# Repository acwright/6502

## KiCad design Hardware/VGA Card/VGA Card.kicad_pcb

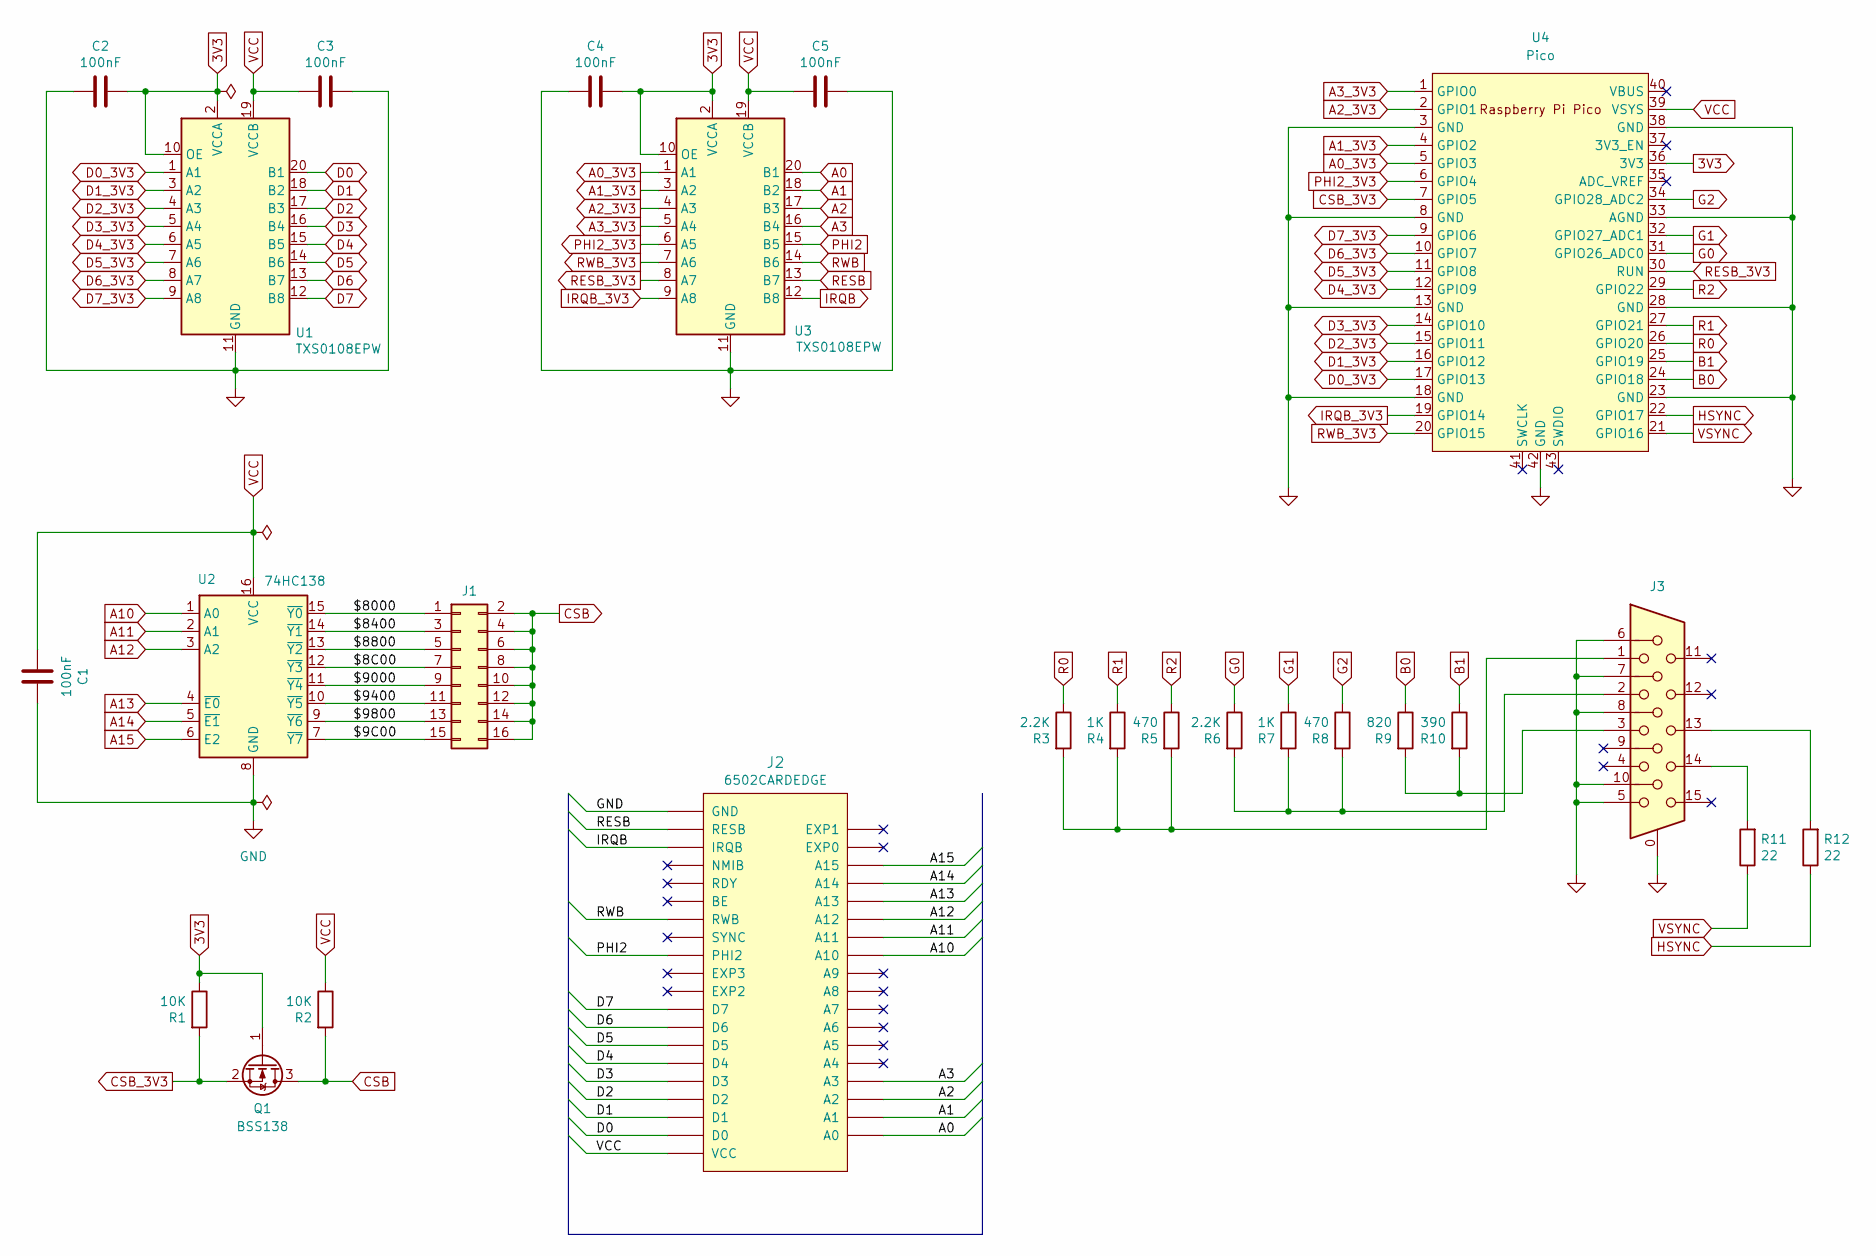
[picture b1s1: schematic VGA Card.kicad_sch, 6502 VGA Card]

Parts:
C1, C2, C3, C4, C5: 100nF; C_0805_2012Metric; LCSC C49678
J1: Conn_02x08_Odd_Even; PinHeader_2x08_P2.54mm_Vertical
J2: 6502CARDEDGE
J3: DE15_Receptacle_HighDensity_MountingHoles; DSUB-15-HD_Female_Horizontal_P2.29x1.98mm_EdgePinOffset3.03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
Q1: BSS138; SOT-23; LCSC C78284
R1, R2: 10K; R_0805_2012Metric; LCSC C17414
R3, R6: 2.2K; R_0805_2012Metric; LCSC C17520
R4, R7: 1K; R_0805_2012Metric; LCSC C17513
R5, R8: 470; R_0805_2012Metric; LCSC C17710
R9: 820; R_0805_2012Metric; LCSC C17837
R10: 390; R_0805_2012Metric; LCSC C17655
R11, R12: 22; R_0805_2012Metric; LCSC C17561
U1, U3: TXS0108EPW; TSSOP-20_4.4x6.5mm_P0.65mm; LCSC C17206
U2: 74HC138; SOIC-16_3.9x9.9mm_P1.27mm; LCSC C5602
U4: Pico; RPi_Pico_SMD_TH

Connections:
3V3: C2.1, C4.1, Q1.1 (G), R1.1, U1.2 (VCCA), U1.10 (OE), U3.2 (VCCA), U3.10 (OE), U4.36 (3V3)
/$8C00: J1.7, U2.12 (~Y3)
/$9C00: J1.15, U2.7 (~Y7)
/$8000: J1.1, U2.15 (~Y0)
/$8400: J1.3, U2.14 (~Y1)
/$8800: J1.5, U2.13 (~Y2)
/$9000: J1.9, U2.11 (~Y4)
/$9400: J1.11, U2.10 (~Y5)
/$9800: J1.13, U2.9 (~Y6)
A0: J2.A0, U3.20 (B1)
A0_3V3: U3.1 (A1), U4.5 (GPIO3)
A1: J2.A1, U3.18 (B2)
A1_3V3: U3.3 (A2), U4.4 (GPIO2)
A2: J2.A2, U3.17 (B3)
A2_3V3: U3.4 (A3), U4.2 (GPIO1)
A3: J2.A3, U3.16 (B4)
A3_3V3: U3.5 (A4), U4.1 (GPIO0)
A10: J2.A10, U2.1 (A0)
A11: J2.A11, U2.2 (A1)
A12: J2.A12, U2.3 (A2)
A13: J2.A13, U2.4 (~E0)
A14: J2.A14, U2.5 (~E1)
A15: J2.A15, U2.6 (E2)
B0: R9.1, U4.24 (GPIO18)
B1: R10.1, U4.25 (GPIO19)
CSB: J1.2, J1.4, J1.6, J1.8, J1.10, J1.12, J1.14, J1.16, Q1.3 (D), R2.2
CSB_3V3: Q1.2 (S), R1.2, U4.7 (GPIO5)
D0: J2.D0, U1.20 (B1)
D0_3V3: U1.1 (A1), U4.17 (GPIO13)
D1: J2.D1, U1.18 (B2)
D1_3V3: U1.3 (A2), U4.16 (GPIO12)
D2: J2.D2, U1.17 (B3)
D2_3V3: U1.4 (A3), U4.15 (GPIO11)
D3: J2.D3, U1.16 (B4)
D3_3V3: U1.5 (A4), U4.14 (GPIO10)
D4: J2.D4, U1.15 (B5)
D4_3V3: U1.6 (A5), U4.12 (GPIO9)
D5: J2.D5, U1.14 (B6)
D5_3V3: U1.7 (A6), U4.11 (GPIO8)
D6: J2.D6, U1.13 (B7)
D6_3V3: U1.8 (A7), U4.10 (GPIO7)
D7: J2.D7, U1.12 (B8)
D7_3V3: U1.9 (A8), U4.9 (GPIO6)
G0: R6.1, U4.31 (GPIO26_ADC0)
G1: R7.1, U4.32 (GPIO27_ADC1)
G2: R8.1, U4.34 (GPIO28_ADC2)
GND: C1.2, C2.2, C3.1, C4.2, C5.1, J2.GND, J3.0, J3.5, J3.6, J3.7, J3.8, J3.10, U1.11 (GND), U2.8 (GND), U3.11 (GND), U4.3 (GND), U4.8 (GND), U4.13 (GND), U4.18 (GND), U4.23 (GND), U4.28 (GND), U4.33 (AGND), U4.38 (GND), U4.42 (GND)
HSYNC: R12.1, U4.22 (GPIO17)
IRQB: J2.IRQB, U3.12 (B8)
IRQB_3V3: U3.9 (A8), U4.19 (GPIO14)
unnamed: J3.1, R3.2, R4.2, R5.2
unnamed: J3.2, R6.2, R7.2, R8.2
unnamed: J3.3, R9.2, R10.2
unnamed: J3.13, R12.2
unnamed: J3.14, R11.2
PHI2: J2.PHI2, U3.15 (B5)
PHI2_3V3: U3.6 (A5), U4.6 (GPIO4)
R0: R3.1, U4.26 (GPIO20)
R1: R4.1, U4.27 (GPIO21)
R2: R5.1, U4.29 (GPIO22)
RESB: J2.RESB, U3.13 (B7)
RESB_3V3: U3.8 (A7), U4.30 (RUN)
RWB: J2.RWB, U3.14 (B6)
RWB_3V3: U3.7 (A6), U4.20 (GPIO15)
VCC: C1.1, C3.2, C5.2, J2.VCC, R2.1, U1.19 (VCCB), U2.16 (VCC), U3.19 (VCCB), U4.39 (VSYS)
VSYNC: R11.1, U4.21 (GPIO16)

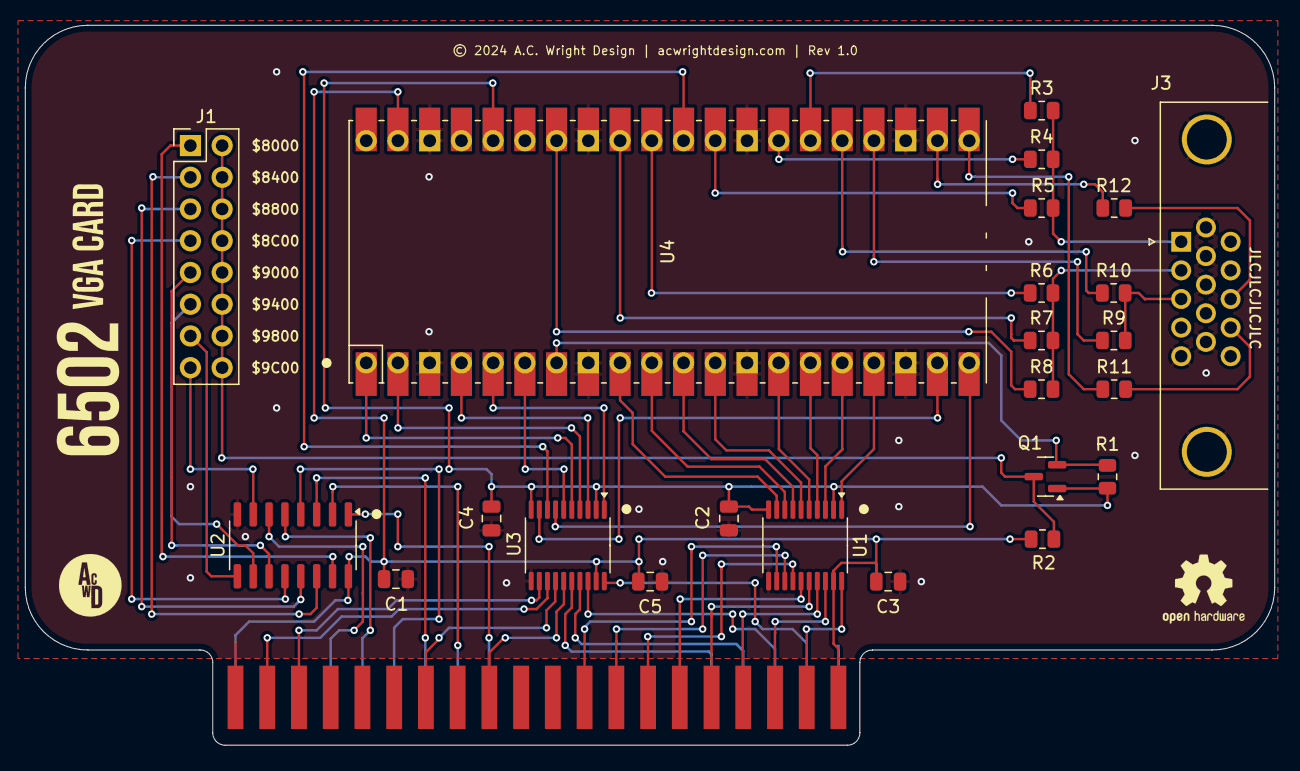
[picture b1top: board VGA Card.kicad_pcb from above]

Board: 2 copper layers, 100.0 x 57.6 mm, 25 parts (0 on the bottom side), 66 nets.

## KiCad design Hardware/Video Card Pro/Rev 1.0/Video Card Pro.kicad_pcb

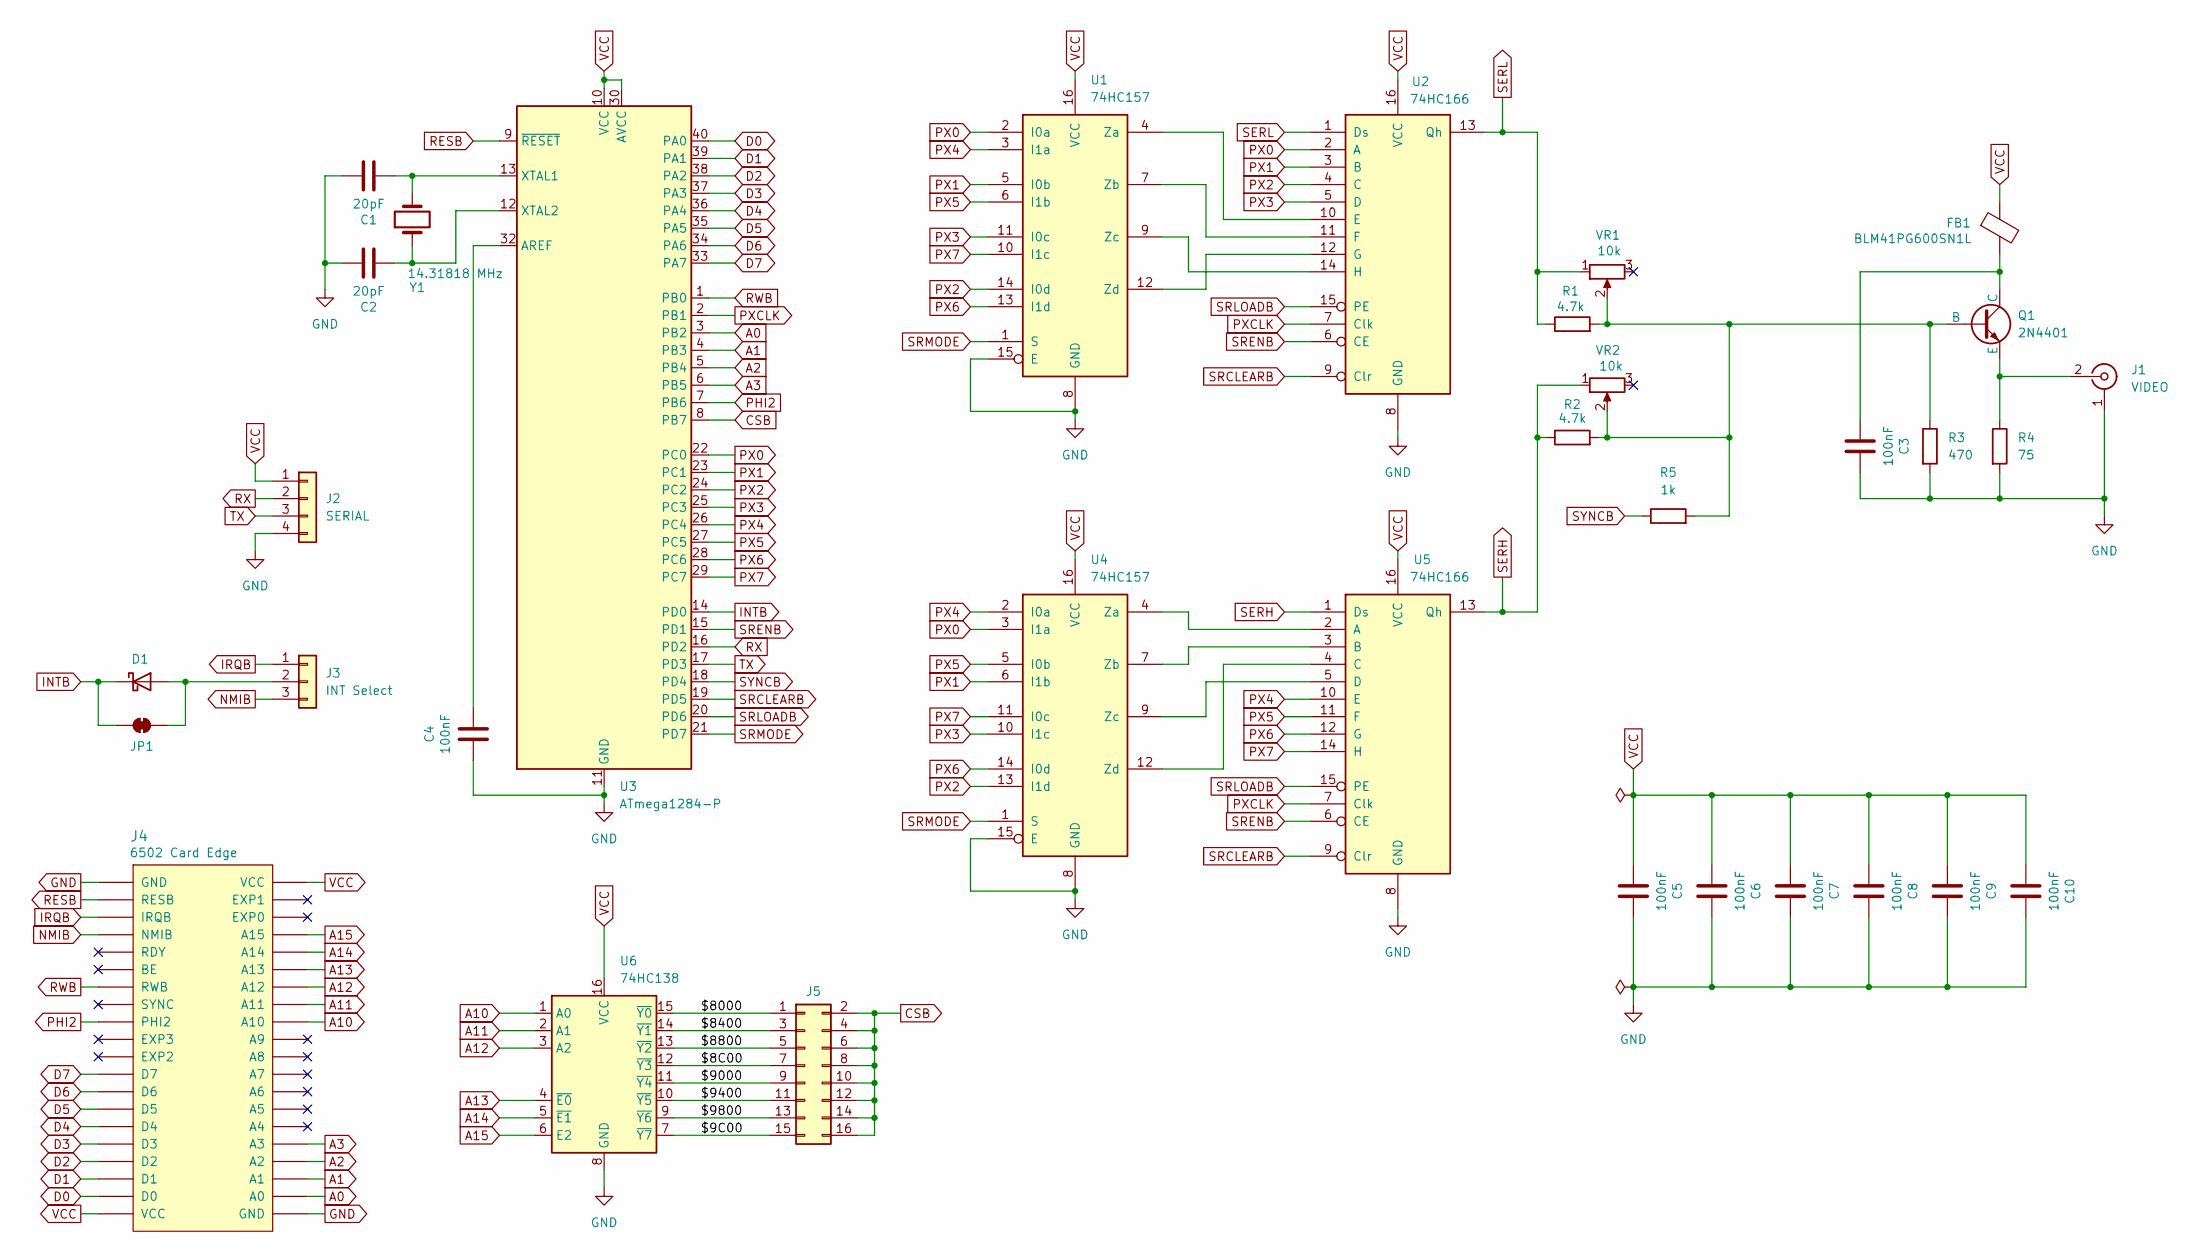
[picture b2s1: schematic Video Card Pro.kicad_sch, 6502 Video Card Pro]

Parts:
C1, C2: 20pF; C_Disc_D5.0mm_W2.5mm_P2.50mm; LCSC C105173
C3, C4, C5, C6, C7, C8, C9, C10: 100nF; C_0805_2012Metric; LCSC C49678
D1: D_Schottky; D_DO-35_SOD27_P7.62mm_Horizontal
FB1: BLM41PG600SN1L; L_1806_4516Metric; LCSC C85844
J1: VIDEO; SWITCHCRAFT_PJRAN1X1U04X
J2: SERIAL; PinHeader_1x04_P2.54mm_Vertical
J3: INT Select; PinHeader_1x03_P2.54mm_Vertical
J4: 6502 Card Edge
J5: Conn_02x08_Odd_Even; PinHeader_2x08_P2.54mm_Vertical
JP1: SolderJumper_2_Bridged; SolderJumper-2_P1.3mm_Bridged_RoundedPad1.0x1.5mm
Q1: 2N4401; TO-92_HandSolder
R1, R2: 4.7k; R_Axial_DIN0204_L3.6mm_D1.6mm_P5.08mm_Horizontal
R3: 470; R_0805_2012Metric; LCSC C17710
R4: 75; R_0805_2012Metric; LCSC C17820
R5: 1k; R_Axial_DIN0204_L3.6mm_D1.6mm_P5.08mm_Horizontal
U1, U4: 74HC157; SOIC-16_3.9x9.9mm_P1.27mm; LCSC C6823
U2, U5: 74HC166; SOIC-16_3.9x9.9mm_P1.27mm; LCSC C473363
U3: ATmega1284-P; DIP-40_W15.24mm_Socket_LongPads
U6: 74HC138; SOIC-16_3.9x9.9mm_P1.27mm; LCSC C5602
VR1, VR2: 10k; 3386F-1-103LF
Y1: 14.31818 MHz; Crystal_HC49-U_Vertical; Mouser 774-MP107-E

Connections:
/$8C00: J5.7, U6.12 (~Y3)
/$9C00: J5.15, U6.7 (~Y7)
/$8000: J5.1, U6.15 (~Y0)
/$8400: J5.3, U6.14 (~Y1)
/$8800: J5.5, U6.13 (~Y2)
/$9000: J5.9, U6.11 (~Y4)
/$9400: J5.11, U6.10 (~Y5)
/$9800: J5.13, U6.9 (~Y6)
A0: J4.A0, U3.3 (PB2)
A1: J4.A1, U3.4 (PB3)
A2: J4.A2, U3.5 (PB4)
A3: J4.A3, U3.6 (PB5)
A10: J4.A10, U6.1 (A0)
A11: J4.A11, U6.2 (A1)
A12: J4.A12, U6.3 (A2)
A13: J4.A13, U6.4 (~E0)
A14: J4.A14, U6.5 (~E1)
A15: J4.A15, U6.6 (E2)
CSB: J5.2, J5.4, J5.6, J5.8, J5.10, J5.12, J5.14, J5.16, U3.8 (PB7)
D0: J4.D0, U3.40 (PA0)
D1: J4.D1, U3.39 (PA1)
D2: J4.D2, U3.38 (PA2)
D3: J4.D3, U3.37 (PA3)
D4: J4.D4, U3.36 (PA4)
D5: J4.D5, U3.35 (PA5)
D6: J4.D6, U3.34 (PA6)
D7: J4.D7, U3.33 (PA7)
GND: C1.2, C2.2, C3.2, C4.1, C5.2, C6.2, C7.2, C8.2, C9.2, C10.2, J1.1 (Ext), J2.4, J4.GND, R3.2, R4.2, U1.8 (GND), U1.15 (E), U2.8 (GND), U3.11 (GND), U3.31 (GND), U4.8 (GND), U4.15 (E), U5.8 (GND), U6.8 (GND)
INTB: D1.1 (K), JP1.1 (A), U3.14 (PD0)
IRQB: J3.1, J4.IRQB
NMIB: J3.3, J4.NMIB
unnamed: D1.2 (A), J3.2, JP1.2 (B)
unnamed: J1.2 (In), Q1.3 (E), R4.1
unnamed: Q1.2 (B), R1.2, R2.2, R3.1, R5.2, VR1.2, VR2.2
unnamed: C3.1, FB1.2, Q1.1 (C)
unnamed: U1.4 (Za), U2.10 (E)
unnamed: U1.7 (Zb), U2.11 (F)
unnamed: U1.9 (Zc), U2.14 (H)
unnamed: U1.12 (Zd), U2.12 (G)
unnamed: C4.2, U3.32 (AREF)
unnamed: C1.1, U3.13 (XTAL1), Y1.2
unnamed: C2.1, U3.12 (XTAL2), Y1.1
unnamed: U4.4 (Za), U5.2 (A)
unnamed: U4.7 (Zb), U5.3 (B)
unnamed: U4.9 (Zc), U5.5 (D)
unnamed: U4.12 (Zd), U5.4 (C)
PHI2: J4.PHI2, U3.7 (PB6)
PX0: U1.2 (I0a), U2.2 (A), U3.22 (PC0), U4.3 (I1a)
PX1: U1.5 (I0b), U2.3 (B), U3.23 (PC1), U4.6 (I1b)
PX2: U1.14 (I0d), U2.4 (C), U3.24 (PC2), U4.13 (I1d)
PX3: U1.11 (I0c), U2.5 (D), U3.25 (PC3), U4.10 (I1c)
PX4: U1.3 (I1a), U3.26 (PC4), U4.2 (I0a), U5.10 (E)
PX5: U1.6 (I1b), U3.27 (PC5), U4.5 (I0b), U5.11 (F)
PX6: U1.13 (I1d), U3.28 (PC6), U4.14 (I0d), U5.12 (G)
PX7: U1.10 (I1c), U3.29 (PC7), U4.11 (I0c), U5.14 (H)
PXCLK: U2.7 (Clk), U3.2 (PB1), U5.7 (Clk)
RESB: J4.RESB, U3.9 (~RESET)
RWB: J4.RWB, U3.1 (PB0)
RX: J2.2, U3.16 (PD2)
SERH: R2.1, U5.1 (Ds), U5.13 (Qh), VR2.1
SERL: R1.1, U2.1 (Ds), U2.13 (Qh), VR1.1
SRCLEARB: U2.9 (Clr), U3.19 (PD5), U5.9 (Clr)
SRENB: U2.6 (CE), U3.15 (PD1), U5.6 (CE)
SRLOADB: U2.15 (PE), U3.20 (PD6), U5.15 (PE)
SRMODE: U1.1 (S), U3.21 (PD7), U4.1 (S)
SYNCB: R5.1, U3.18 (PD4)
TX: J2.3, U3.17 (PD3)
VCC: C5.1, C6.1, C7.1, C8.1, C9.1, C10.1, FB1.1, J2.1, J4.VCC, U1.16 (VCC), U2.16 (VCC), U3.10 (VCC), U3.30 (AVCC), U4.16 (VCC), U5.16 (VCC), U6.16 (VCC)

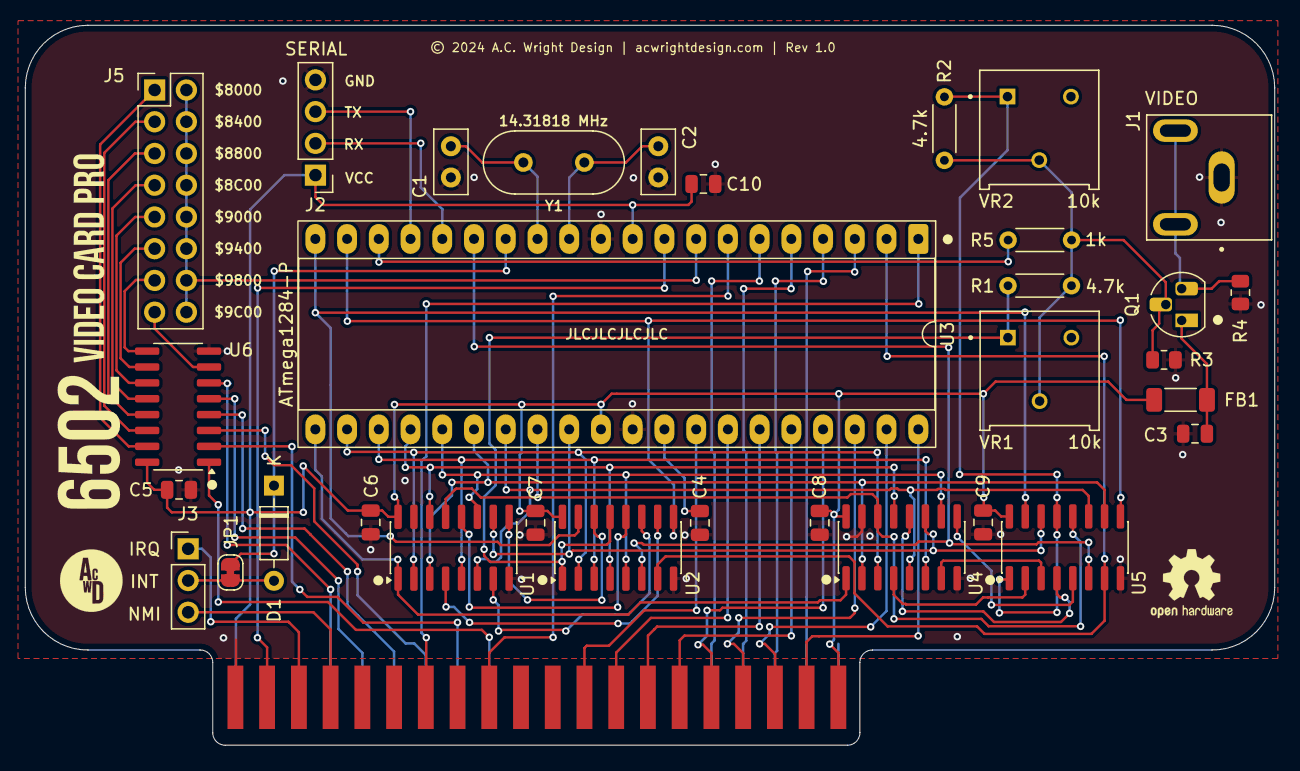
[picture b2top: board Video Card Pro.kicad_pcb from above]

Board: 2 copper layers, 100.0 x 57.6 mm, 33 parts (0 on the bottom side), 68 nets.

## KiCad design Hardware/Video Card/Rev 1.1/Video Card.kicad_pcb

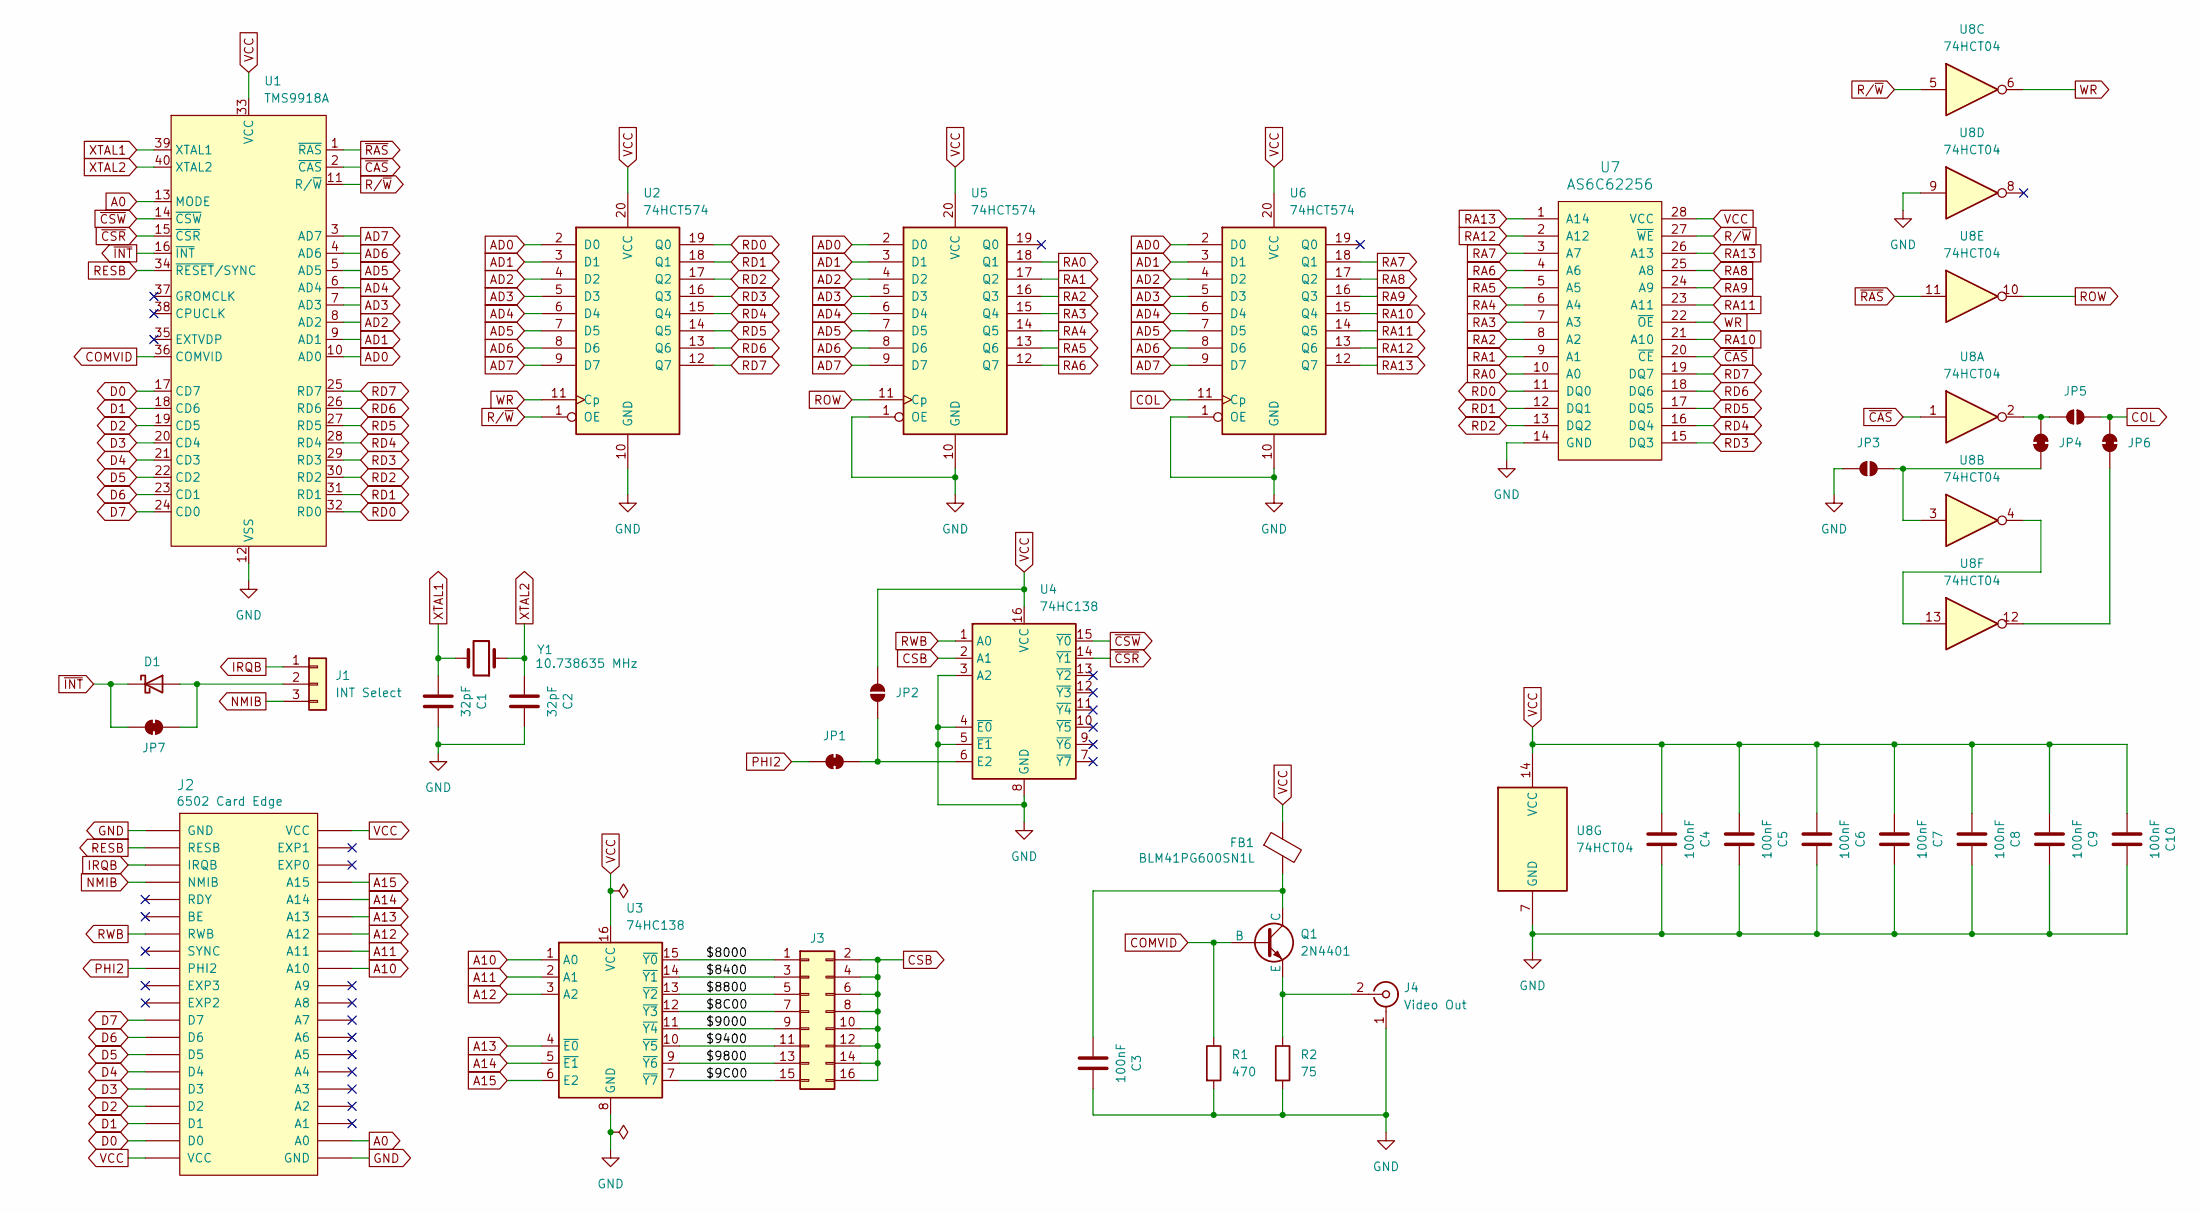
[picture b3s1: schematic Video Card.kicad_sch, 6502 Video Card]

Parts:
C1, C2: 32pF; C_Disc_D5.0mm_W2.5mm_P2.50mm; LCSC C107114
C3, C4, C5, C6, C7, C8, C9, C10: 100nF; C_0805_2012Metric; LCSC C49678
D1: D_Schottky; D_DO-35_SOD27_P7.62mm_Horizontal
FB1: BLM41PG600SN1L; L_1806_4516Metric; LCSC C85844
J1: INT Select; PinHeader_1x03_P2.54mm_Vertical
J2: 6502 Card Edge
J3: Conn_02x08_Odd_Even; PinHeader_2x08_P2.54mm_Vertical
J4: Video Out; SWITCHCRAFT_PJRAN1X1U04X
JP1, JP4, JP6, JP7: SolderJumper_2_Bridged; SolderJumper-2_P1.3mm_Bridged_RoundedPad1.0x1.5mm
JP2, JP3, JP5: SolderJumper_2_Open; SolderJumper-2_P1.3mm_Open_RoundedPad1.0x1.5mm
Q1: 2N4401; TO-92_HandSolder
R1: 470; R_0805_2012Metric; LCSC C17710
R2: 75; R_0805_2012Metric; LCSC C17820
U1: TMS9918A; DIP-40_W15.24mm_Socket_LongPads
U2, U5, U6: 74HCT574; SOIC-20W_7.5x12.8mm_P1.27mm; LCSC C6001
U3, U4: 74HC138; SOIC-16_3.9x9.9mm_P1.27mm; LCSC C5602
U7: AS6C62256; DIP-28_W15.24mm_Socket_LongPads
U8: 74HCT04; SO-14_3.9x8.65mm_P1.27mm; LCSC C672096
Y1: 10.738635 MHz; Crystal_HC49-U_Vertical; Mouser 774-MP107-E

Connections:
/$8C00: J3.7, U3.12 (~Y3)
/$9C00: J3.15, U3.7 (~Y7)
/$8000: J3.1, U3.15 (~Y0)
/$8400: J3.3, U3.14 (~Y1)
/$8800: J3.5, U3.13 (~Y2)
/$9000: J3.9, U3.11 (~Y4)
/$9400: J3.11, U3.10 (~Y5)
/$9800: J3.13, U3.9 (~Y6)
A0: J2.A0, U1.13 (MODE)
A10: J2.A10, U3.1 (A0)
A11: J2.A11, U3.2 (A1)
A12: J2.A12, U3.3 (A2)
A13: J2.A13, U3.4 (~E0)
A14: J2.A14, U3.5 (~E1)
A15: J2.A15, U3.6 (E2)
AD0: U1.10 (AD0), U2.2 (D0), U5.2 (D0), U6.2 (D0)
AD1: U1.9 (AD1), U2.3 (D1), U5.3 (D1), U6.3 (D1)
AD2: U1.8 (AD2), U2.4 (D2), U5.4 (D2), U6.4 (D2)
AD3: U1.7 (AD3), U2.5 (D3), U5.5 (D3), U6.5 (D3)
AD4: U1.6 (AD4), U2.6 (D4), U5.6 (D4), U6.6 (D4)
AD5: U1.5 (AD5), U2.7 (D5), U5.7 (D5), U6.7 (D5)
AD6: U1.4 (AD6), U2.8 (D6), U5.8 (D6), U6.8 (D6)
AD7: U1.3 (AD7), U2.9 (D7), U5.9 (D7), U6.9 (D7)
COL: JP5.1 (A), JP6.2 (B), U6.11 (Cp)
COMVID: Q1.2 (B), R1.1, U1.36 (COMVID)
CSB: J3.2, J3.4, J3.6, J3.8, J3.10, J3.12, J3.14, J3.16, U4.2 (A1)
D0: J2.D0, U1.17 (CD7)
D1: J2.D1, U1.18 (CD6)
D2: J2.D2, U1.19 (CD5)
D3: J2.D3, U1.20 (CD4)
D4: J2.D4, U1.21 (CD3)
D5: J2.D5, U1.22 (CD2)
D6: J2.D6, U1.23 (CD1)
D7: J2.D7, U1.24 (CD0)
GND: C1.2, C2.2, C3.2, C4.2, C5.2, C6.2, C7.2, C8.2, C9.2, C10.2, J2.GND, J4.1 (Ext), JP3.2 (B), R1.2, R2.2, U1.12 (VSS), U2.10 (GND), U3.8 (GND), U4.3 (A2), U4.4 (~E0), U4.5 (~E1), U4.8 (GND), U5.1 (OE), U5.10 (GND), U6.1 (OE), U6.10 (GND), U7.14 (GND), U8.7 (GND), U8.9
IRQB: J1.1, J2.IRQB
NMIB: J1.3, J2.NMIB
unnamed: D1.2 (A), J1.2, JP7.2 (B)
unnamed: J4.2 (In), Q1.3 (E), R2.1
unnamed: JP1.1 (A), JP2.2 (B), U4.6 (E2)
unnamed: JP3.1 (A), JP4.1 (A), U8.3
unnamed: JP4.2 (B), JP5.2 (B), U8.2
unnamed: JP6.1 (A), U8.12
unnamed: C3.1, FB1.2, Q1.1 (C)
unnamed: U8.4, U8.13
PHI2: J2.PHI2, JP1.2 (B)
RA0: U5.18 (Q1), U7.10 (A0)
RA1: U5.17 (Q2), U7.9 (A1)
RA2: U5.16 (Q3), U7.8 (A2)
RA3: U5.15 (Q4), U7.7 (A3)
RA4: U5.14 (Q5), U7.6 (A4)
RA5: U5.13 (Q6), U7.5 (A5)
RA6: U5.12 (Q7), U7.4 (A6)
RA7: U6.18 (Q1), U7.3 (A7)
RA8: U6.17 (Q2), U7.25 (A8)
RA9: U6.16 (Q3), U7.24 (A9)
RA10: U6.15 (Q4), U7.21 (A10)
RA11: U6.14 (Q5), U7.23 (A11)
RA12: U6.13 (Q6), U7.2 (A12)
RA13: U6.12 (Q7), U7.1 (A14), U7.26 (A13)
RD0: U1.32 (RD0), U2.19 (Q0), U7.11 (DQ0)
RD1: U1.31 (RD1), U2.18 (Q1), U7.12 (DQ1)
RD2: U1.30 (RD2), U2.17 (Q2), U7.13 (DQ2)
RD3: U1.29 (RD3), U2.16 (Q3), U7.15 (DQ3)
RD4: U1.28 (RD4), U2.15 (Q4), U7.16 (DQ4)
RD5: U1.27 (RD5), U2.14 (Q5), U7.17 (DQ5)
RD6: U1.26 (RD6), U2.13 (Q6), U7.18 (DQ6)
RD7: U1.25 (RD7), U2.12 (Q7), U7.19 (DQ7)
RESB: J2.RESB, U1.34 (~RESET/SYNC)
ROW: U5.11 (Cp), U8.10
RWB: J2.RWB, U4.1 (A0)
R/~W: U1.11 (R/~W), U2.1 (OE), U7.27 (~WE), U8.5
VCC: C4.1, C5.1, C6.1, C7.1, C8.1, C9.1, C10.1, FB1.1, J2.VCC, JP2.1 (A), U1.33 (VCC), U2.20 (VCC), U3.16 (VCC), U4.16 (VCC), U5.20 (VCC), U6.20 (VCC), U7.28 (VCC), U8.14 (VCC)
WR: U2.11 (Cp), U7.22 (~OE), U8.6
XTAL1: C1.1, U1.39 (XTAL1), Y1.2
XTAL2: C2.1, U1.40 (XTAL2), Y1.1
~CAS: U1.2 (~CAS), U7.20 (~CE), U8.1
~CSR: U1.15 (~CSR), U4.14 (~Y1)
~CSW: U1.14 (~CSW), U4.15 (~Y0)
~INT: D1.1 (K), JP7.1 (A), U1.16 (~INT)
~RAS: U1.1 (~RAS), U8.11

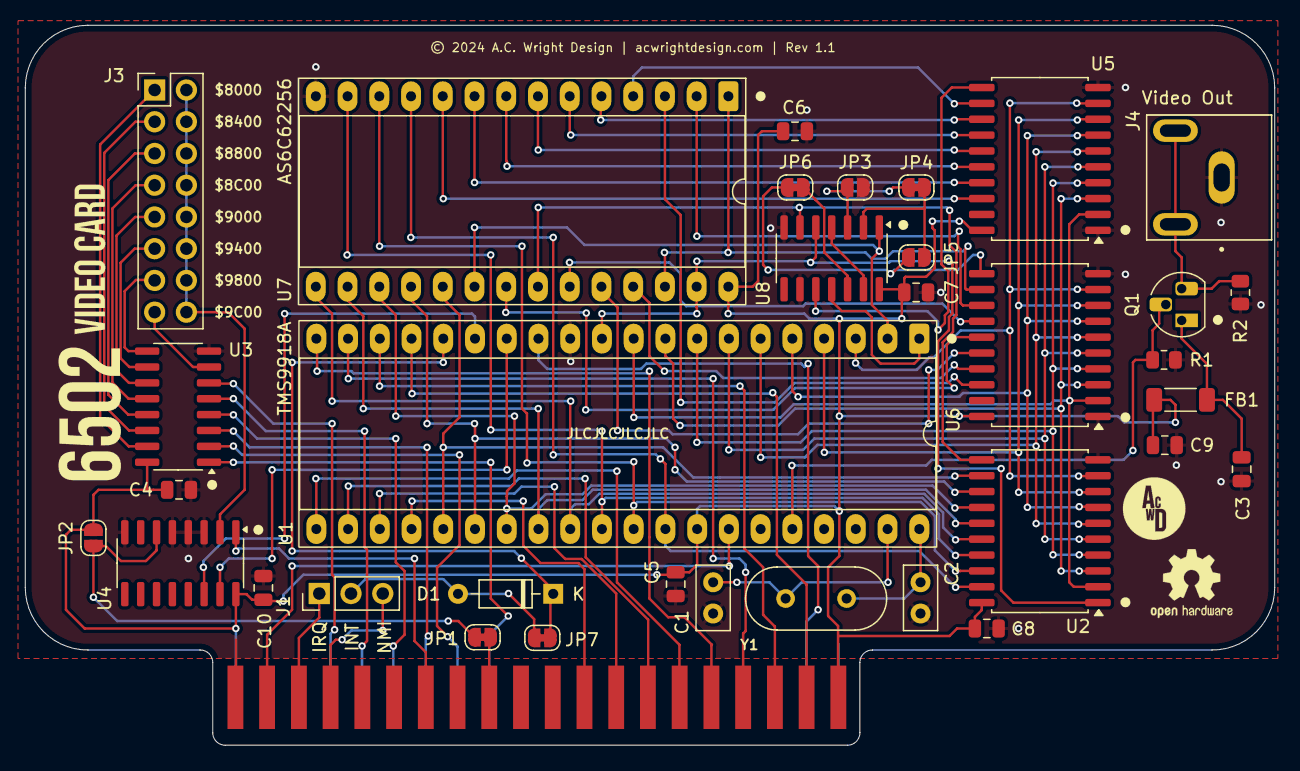
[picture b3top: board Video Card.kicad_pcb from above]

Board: 2 copper layers, 100.0 x 57.6 mm, 35 parts (0 on the bottom side), 81 nets.

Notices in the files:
Hardware/VGA Card/VGA Card.kicad_pcb:
© 2024 A.C. Wright Design | acwrightdesign.com | Rev 1.0
Hardware/Video Card/Rev 1.1/Video Card.kicad_pcb:
© 2024 A.C. Wright Design | acwrightdesign.com | Rev 1.1
